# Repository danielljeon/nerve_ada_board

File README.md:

# nerve_ada_board

Nerve dev board using off-the-shelf modules.

> **Note: This design is now no longer under active development.** The final
> changes to the main branch are published as release tagged `v0.1.0-beta`, see
> the release notes: [1.1 v0.1.0-beta](#11-v010-beta).
>
> Successor: [`nerve_pcb`](https://github.com/danielljeon/nerve_pcb).

> 💡**Hint:** To clone this repository use:
> ```shell
> git clone --recursive
> ```

---

|                   KiCad Render                   |                   `v0.1.0-alpha-7b18788`                   |
|:------------------------------------------------:|:----------------------------------------------------------:|
|  |  |

---

<details markdown="1">
  <summary>Table of Contents</summary>

<!-- TOC -->
* [nerve_ada_board](#nerve_ada_board)
  * [1 Release Notes](#1-release-notes)
    * [1.1 v0.1.0-beta](#11-v010-beta)
      * [1.1.1 LSE Crystal](#111-lse-crystal)
      * [1.1.2 External Clock Crystal Tuning](#112-external-clock-crystal-tuning)
      * [1.1.3 GPS](#113-gps)
  * [2 Overview](#2-overview)
    * [2.1 Function Connectors](#21-function-connectors)
    * [2.2 Switches & Jumpers](#22-switches--jumpers)
    * [2.3 Plug-in Modules](#23-plug-in-modules)
    * [2.4 Breakout Connectors](#24-breakout-connectors)
  * [3 Development](#3-development)
    * [3.1 Worflow](#31-worflow)
    * [3.2 Submodules](#32-submodules)
  * [4 Production History](#4-production-history)
    * [4.1 v0.1.0-alpha-7b18788](#41-v010-alpha-7b18788)
<!-- TOC -->

</details>

---

## 1 Release Notes

### 1.1 v0.1.0-beta

Following the initial validation of components and software on this PCB design,
development has shifted to a more production-oriented
board: [nerve_pcb](https://github.com/danielljeon/nerve_pcb). While the base
components remain similar, many have been modified, with further
changes expected.

During the development of the new design, several hardware and PCB issues were
identified. Although this `README.md` will no longer be updated, the following
sections document the known issues as of the final release.

`v0.1.0-beta` is a slightly improved and updated version of an earlier
production run using `v0.1.0-alpha-7b18788`,
see [4.1 v0.1.0-alpha-7b18788](#41-v010-alpha-7b18788).

#### 1.1.1 LSE Crystal

The current LSE crystal on the STM32F446RE is the ABS25-32.768KHZ-6-T.

This is not the intended component; the correct crystal should have been the
`ABS25-32.768KHZ-T`, which has a more appropriate load capacitance specification
of 12.5 pF. The `ABS25-32.768KHZ-6-T` variant, with a 6 pF load capacitance, was
used inadvertently.

#### 1.1.2 External Clock Crystal Tuning

The crystal circuits use calculated capacitors that have not yet been fully
verified or fine-tuned. Specifically, the 32.768 kHz LSE crystal is likely using
incorrect capacitors with a value of 1.5 pF.

#### 1.1.3 GPS

The GPS module (`SAM-M10Q`) had not been verified to be functional as of the
release. However, this is likely due to software limitations rather than issues
with the hardware or PCB design.

---

## 2 Overview

Development board for the STM32
based [nerve](https://github.com/danielljeon/nerve) controller firmware.

### 2.1 Function Connectors

These connectors are fixed by hardware (PCB traces or the connector itself).

| Connector             | Ref | Description                                                                    |
|-----------------------|:---:|--------------------------------------------------------------------------------|
| Tag-Connect TC2050    | J1  | Programming/debug connector                                                    |
| Hinge microSD Card    | J2  | Portable storage, see [Molex product video](https://youtu.be/YY2V8z6UK7M?t=95) |
| USB-C 5 V Power       | J3  | Power only USB-C, primary 5 V source                                           |
| CR1220 Battery        | BT1 | MCU and GPS battery source 3.3 V supply                                        |
| CAN1 (Transceiver U7) | J7  | Pin 1: CAN1 High, Pin 2: CAN1 Low                                              |
| CAN2 (Transceiver U8) | J8  | Pin 1: CAN2 High, Pin 2: CAN2 Low                                              |

### 2.2 Switches & Jumpers

User controllable hardware and/or firmware driven inputs.

| Switch/Jumper           | Ref | Description                                    |
|-------------------------|:---:|------------------------------------------------|
| MCU NRESET Switch       | SW1 | Generic 6 mm TH button, push to reset          |
| MCU PA0 Switch          | SW2 | Generic 6 mm TH button, designed for SYS_WKUP0 |
| MCU PC13 Switch         | SW3 | Generic 6 mm TH button, designed for SYS_WKUP1 |
| SDIO Card Detect Jumper | J4  | Close for card inserted (pull-down on close)   |
| BOOT0 Jumper            | J5  | Open for run flash memory (pull-down on open)  |

### 2.3 Plug-in Modules

Off-the-shelf plug-in boards, primarily from Adafruit.

| Manufacturer Part Number |  Ref   | Manufacturer            | Hardware Interface | Quantity | Description                      |
|--------------------------|:------:|-------------------------|--------------------|---------:|----------------------------------|
| 4816                     |   U3   | Adafruit Industries LLC | 2.54 mm pitch TH   |        1 | BMP390 Module                    |
| Digi XBee-PRO 900HP      |   U5   | Digi                    | 2 mm pitch TH      |        1 | Long Range 900 MHz OEM RF Module |
| 4754                     |   U6   | Adafruit Industries LLC | 2.54 mm pitch TH   |        1 | BNO085 Module                    |
| 5708                     | U7, U8 | Adafruit Industries LLC | 2.54 mm pitch TH   |        2 | TJA1051T/3 Module                |

### 2.4 Breakout Connectors

Simple breakout connectors, driven fully or partially by firmware. See schematic
and firmware docs for details.

| Connector        | Ref | Logic | Description                                                                                     |
|------------------|:---:|:-----:|-------------------------------------------------------------------------------------------------|
| WS2812B Extender | J6  |  5 V  | Pin 1: PWM, Pin 2: Ground, use separate supply (preventing over current draw) and common ground |
| SPI Breakout     | J9  | 3.3 V | Pin 1: CS, Pin 2: SCK, Pin 3: MISO, Pin 4: MOSI                                                 |
| GPIO Breakout    | J10 |  5 V  | Pin 1, 2, 3: GPIO 1, 2, 3                                                                       |
| PWM Breakout     | J11 |  5 V  | Pin 1, 2: PWM 1, 2                                                                              |
| UART Camera      | J12 |  5 V  | Pin 1: 5 V, Pin 2: UART RX, Pin 3: UART TX, Pin 4: Ground, design for low current camera        |

---

## 3 Development

### 3.1 Worflow

Developed using KiCad with KiBot GitHub Actions
workflow, [kibot.yaml](.github/workflows/kibot.yaml).

- KiBot configurations found in [config.kibot.yaml](config.kibot.yaml).

CI/CD objectives:

1. ERC (Electrical Rule Check).
2. DRC (Design Rule Check).
3. PCB docs.
    - PCB layer docs (`.pdf` and `.svg`).
4. PCB manufacturing.
    - Gerber files (`.grb`).
    - Drill file (`.drl` and `.pdf` reference docs).
5. Assembly (fabrication service & hand assembly).
    - Pick-and-place assembly position file (`.pos`).
    - Component distributor ordering BoM (`.csv`).
    - General BoMs (`.xlsx` and `.html`).
    - Component placement guide (`.html`).
6. CAD.
    - (`.step`).

### 3.2 Submodules

This repository includes the submodule `component_library`, located
at: [component_library](https://github.com/danielljeon/component_library).

When cloning the repository, make sure to use the recursive option:

```shell
git clone --recursive
```

To update the submodule to its latest version in a cloned repository, use the
following command:

> Note: This is not recommended for this deprecated repository, as pulling
> updates from the submodule's latest commit may result in incompatibilities.

```shell
git submodule update --remote --merge
```

---

## 4 Production History

### 4.1 v0.1.0-alpha-7b18788

> Note: This production run was not marked as a (pre)release due to very high
> probability of bring-up issues as it was one of my first PCB designs.

Commit: [7b18788](https://github.com/danielljeon/nerve_ada_board/commit/7b187884c03f280627d8443d2d9cc163f4b6956e).

<details markdown="1">
  <summary>Manufacturing & Assembly Details</summary>

**Manufacturing Information:**

Production date: 2024-10-22.

- Manufacturer: JLCPCB.
- Order: PCB, stencil.
- PCB specs (non-default):
    - PCB quantity: 5.
    - Surface Finish: LeadFree HASL.
    - Impedance control stackup: `JLC041611-7628`.
        - Outer Copper Weight: 1 oz.
        - Inner Copper Weight: 1 oz.
- Stencil specs (non-default):
    - Stencil quantity: 1.
    - Custom size: 100 mm x 100 mm (matching PCB dimensions).

**Assembly Information:**

Assembly date: 2024-11-09 to 2024-11-13.

- Assembled PCB quantity: 2.
- Process:
    - Stencil solder paste print by hand & soldering iron.
        - Solder paste: Chip Quik TS391LT `Bi57.6Sn42Ag0.4`.
    - SMD pick-and-place by hand.
    - Reflow with oven.
        - Roughly correct temperatures to solder paste docs.
        - Approximately doubled soak time due to oven limitations.

1. PCB 1 Notes:
    - Components: All placed except for GPS.
    - Damage to though holes for connector J4 mostly on bottom side.
        - First assembly was unsatisfactory.
        - Attempt to remove solder to reassemble header pins resulted in damage
          from aggressive force with the soldering iron.
        - Final result was functional, but the board damage remains on bottom
          side.
            - Suggested correction: heat soak the board, note also left in board
              evaluation section of this writeup.
        - Continuity tests showed no issues after completion.
    - Bridged pins on the U2 (STM32F446RE).
        - Likely too much solder paste and less than ideal definition of the
          printed solder paste.
        - Resolved with flux and reheat with soldering iron as well as use of
          solder wick.
            - Suggested correction: Cleaner swipe of the stencil with less
              solder paste.
2. PCB 2 Notes:
    - Components: All placed.
    - Misplacement of U2 (STM32F446RE).
        - Component shifted seemingly during reflow, some sides of the MCU had
          short or unconnected pins.
        - There was likely too much solder as well as potential misalignment
          during the pick-and-place by hand.
        - Attempts were made to reposition the component.
        - Some solder mask was removed near the pads, however no significant
          functional concerns were visible.
        - In order to limit potential damage to the board or components (
          particularly the expensive GPS module), the component was removed.
        - No pad damage was visible.
        - A replacement component was hand soldered with a soldering iron.
            - Suggested correction: Improve solder paste printing (again) and
              better hand placement. If too much paste was visible retry before
              any reflow. Perhaps, even holding the component in position with
              thin strips of kapton tape.
    - Bridged pins on the U9, U10 (TXB0104QPWRQ1).
        - Same details as U2 on PCB 1 (see above).
    - U4 GPS module solder joints are not visible (pads under component), but a
      continuity test of nets in every combination pair showed no shorts.

</details>

**Board Evaluation:**

- Large planes, especially ground. It is difficult to adjust through hole
  components that have ground pin(s).
    - Requires heat soaked board or potentially risky soldering iron
      temperatures.
- Some components such as resistors or capacitors are very close to through hole
  header pin connectors/jumpers.
    - Not super difficult to deal with, but something to keep in mind.
- The XBee Pro 900HP can cause clearance issues when trying to press-release the
  nearby TC2050-IDC's plastic clips.
- The Molex 472192001 hinge microSD card slot is functional, but slightly
  blocked by the Adafruit TJA1051T/3 breakout board.
    - This Would be easily resolved by implementing CAN circuit/components
      directly onto the PCB.

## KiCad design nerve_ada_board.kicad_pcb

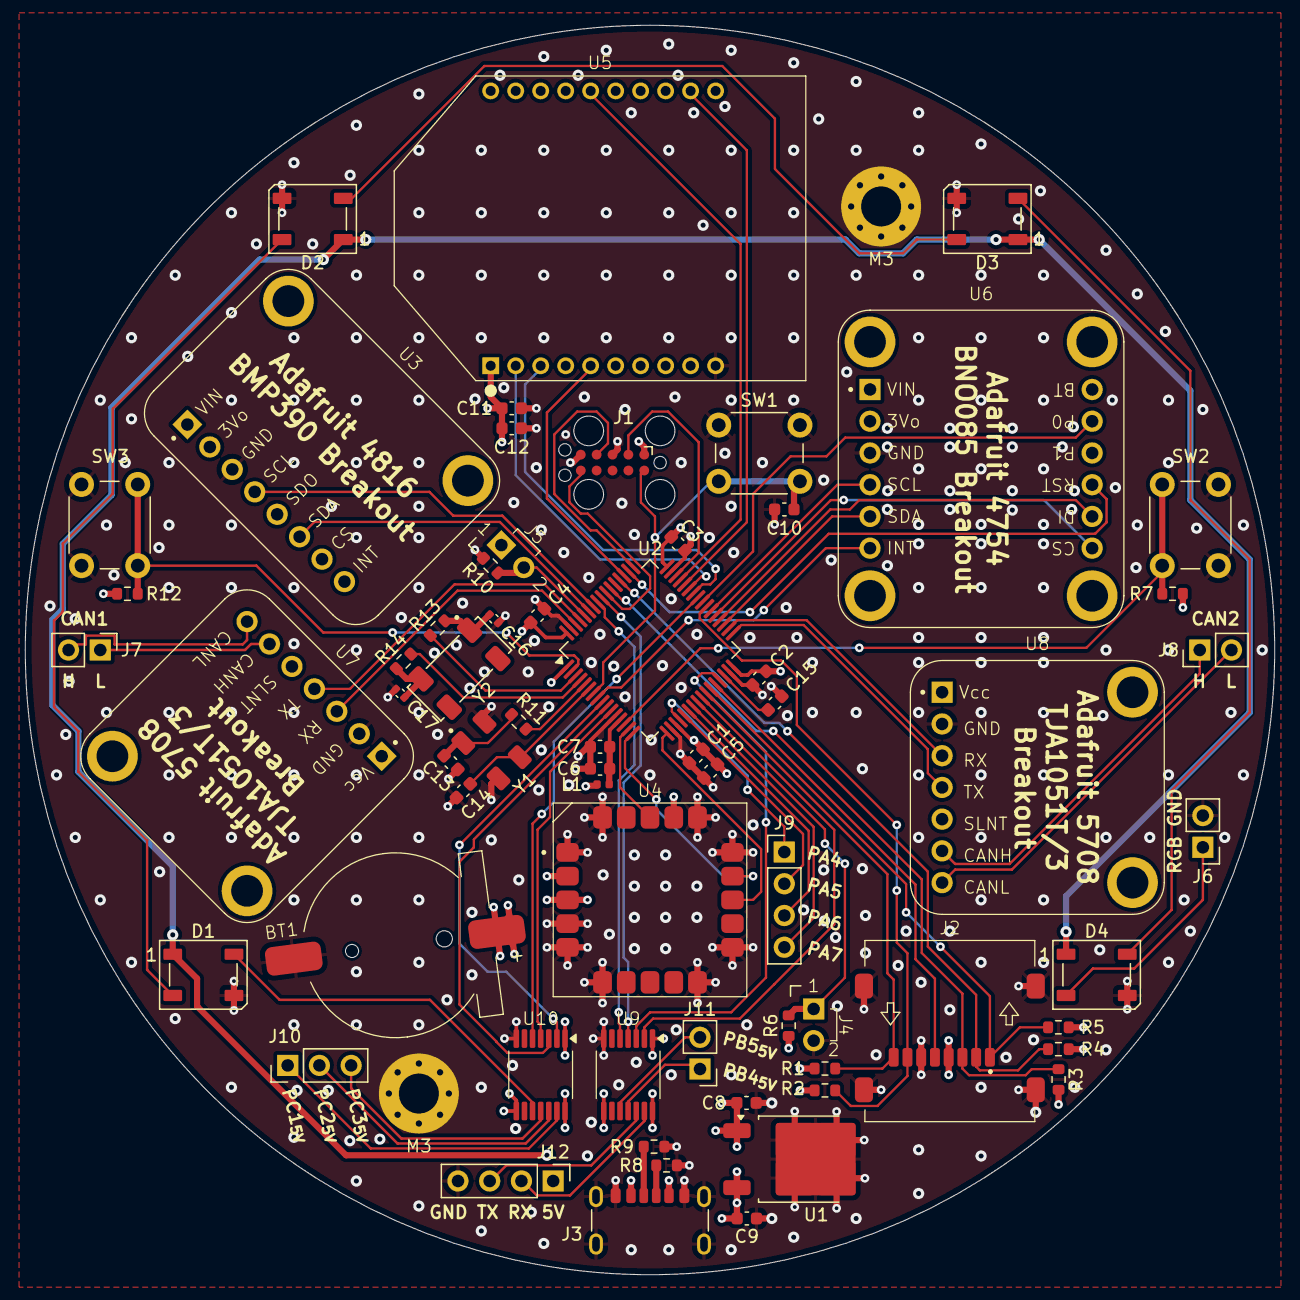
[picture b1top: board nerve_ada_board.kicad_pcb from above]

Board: 4 copper layers, 100.0 x 100.0 mm, 66 parts (0 on the bottom side), 78 nets.

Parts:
BT1: CR1220; harwin_s8411-45r_cr1220_battery
C1, C2, C3, C4, C10: 100n; C_0603_1608Metric
C5: 4u7; C_0603_1608Metric
C6, C8, C12: 1u; C_0603_1608Metric
C7: 10n; C_0603_1608Metric
C9, C15: 2u2; C_0603_1608Metric
C11: 47p; C_0603_1608Metric
C13, C14: 20p; C_0603_1608Metric
C16, C17: 1p5; C_0402_1005Metric
D1, D2, D3, D4: WS2812B; LED_WS2812B_PLCC4_5.0x5.0mm_P3.2mm
H1, H2: M3; MountingHole_3.2mm_M3_Pad_Via
J1: TC2050-IDC; tag_connect_tc2050-idc
J2: 472192001; molex_472192001_microsd_hinge
J3: 2171750001; molex_2171750001_usb_c_6p
J4, J5: harwin_2p_2-54_jumper_open
J6: WS2812B; PinHeader_1x02_P2.54mm_Vertical
J7: CAN1; PinHeader_1x02_P2.54mm_Vertical
J8: CAN2; PinHeader_1x02_P2.54mm_Vertical
J9: PA4-7; PinHeader_1x04_P2.54mm_Vertical
J10: PC1-3; PinHeader_1x03_P2.54mm_Vertical
J11: PB4-5; PinHeader_1x02_P2.54mm_Vertical
J12: Camera; PinHeader_1x04_P2.54mm_Vertical
L1: 39n; L_0402_1005Metric
R1, R2, R3, R4, R5: 47k; R_0603_1608Metric
R6, R7, R10, R12: 10k; R_0603_1608Metric
R8, R9: 5k1; R_0603_1608Metric
R11, R13, R14: 0R; R_0603_1608Metric
SW1, SW2, SW3: SPST; SW_PUSH_6mm
U1: ld39150dt33-r; to-252-2_dpak-2-leg
U2: STM32F446RET; LQFP-64_10x10mm_P0.5mm
U3: adafruit_4816_bmp390
U4: SAM-M10Q; ublox_sam
U5: XBP9B-DMWT-002; xbee_pro_900hp
U6: adafruit_4754_bno085
U7, U8: adafruit_5708_tja1051t-3
U9, U10: TXB0104QPWRQ1; txb0104qpwrq1
Y1: 8M; xtal_abm3b-8.000mhz-10-1-u-t
Y2: 32k768; xtal_abs25-32.768khz-6-t

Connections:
+3.3VA: C6.1, C7.1, L1.2, U2.13 (VDDA)
+3.3VBATT: BT1.2, U2.1 (VBAT), U4.3 (V_BCKP)
+3V3: C1.1, C2.1, C3.1, C4.1, C5.1, C9.1, C11.1, C12.1, J1.1 (VCC), J2.4 (VDD), J5.1, L1.1, R1.1, R2.1, R3.1, R4.1, R5.1, R6.1, R7.1, R12.1, U1.3 (VO), U2.19 (VDD), U2.32 (VDD), U2.48 (VDD), U2.64 (VDD), U3.1 (VIN), U4.2 (V_IO), U4.17 (VCC), U5.1 (VCC), U5.14 (VREF), U6.1 (VIN), U6.10 (P1), U7.1 (Vcc), U8.1 (Vcc), U9.1 (V_{CCA}), U9.8 (OE), U10.1 (V_{CCA}), U10.8 (OE)
+5V: C8.1, D1.1 (VDD), D2.1 (VDD), D3.1 (VDD), D4.1 (VDD), J3.A9 (VBUS), J3.B9 (VBUS), J12.1, U1.1 (VI), U9.14 (V_{CCB}), U10.14 (V_{CCB})
/BOOT0: J5.2, R10.2, U2.60 (BOOT0)
/CAMERA_RX: J12.2, U9.13 (B1)
/CAMERA_TX: J12.3, U9.12 (B2)
/CAN1+: J7.1, U7.6 (CANH)
/CAN1-: J7.2, U7.7 (CANL)
/CAN1_RX: U2.61 (PB8), U7.4 (TX)
/CAN1_TX: U2.62 (PB9), U7.3 (RX)
/CAN2+: J8.1, U8.6 (CANH)
/CAN2-: J8.2, U8.7 (CANL)
/CAN2_RX: U2.33 (PB12), U8.4 (TX)
/CAN2_TX: U2.34 (PB13), U8.3 (RX)
/EXTI0_IMU_INT: U2.8 (PC0), U6.6 (INT)
/GPIO_GPS_RST: U2.15 (PA1), U4.18 (RESET_N)
/GPIO_IMU_P0: U2.40 (PC9), U6.11 (P0)
/GPIO_IMU_RST: U2.50 (PA15), U6.9 (RST)
/GPIO_RADIO_RST: U2.51 (PC10), U5.5 (~RESET)
/GPIO_SPI2_CS: U2.37 (PC6), U6.7 (CS)
/HSE_IN: R11.1, U2.5 (PH0_OSC_HSE_IN)
/HSE_OUT: C14.1, U2.6 (PH1_OSC_HSE_OUT), Y1.3
/I2C1_SCL: U2.58 (PB6), U3.4 (SCL)
/I2C1_SDA: U2.59 (PB7), U3.6 (SDA)
/LSE_IN: R13.1, U2.3 (PC14_OSC32_LSE_IN)
/LSE_OUT: R14.1, U2.4 (PC15_OSC32_LSE_OUT)
/NRST: C10.2, J1.10 (~RESET), SW1.2, U2.7 (NRST)
/PA4: J9.1, U2.20 (PA4)
/PA5: J9.2, U2.21 (PA5)
/PA6: J9.3, U2.22 (PA6)
/PA7: J9.4, U2.23 (PA7)
/PB4: U2.56 (PB4), U9.4 (A3)
/PB4_EXP: J11.1, U9.11 (B3)
/PB5: U2.57 (PB5), U9.5 (A4)
/PB5_EXP: J11.2, U9.10 (B4)
/PC1: U2.9 (PC1), U10.2 (A1)
/PC1_EXP: J10.1, U10.13 (B1)
/PC2: U2.10 (PC2), U10.3 (A2)
/PC2_EXP: J10.2, U10.12 (B2)
/PC3: U2.11 (PC3), U10.4 (A3)
/PC3_EXP: J10.3, U10.11 (B3)
/RGB_LED: D1.4 (DIN), U10.10 (B4)
/SDIO_CLK: J2.5 (CLK), U2.28 (PB2)
/SDIO_CMD: J2.3 (CMD), R3.2, U2.54 (PD2)
/SDIO_D0: J2.7 (DAT0), R2.2, U2.39 (PC8)
/SDIO_D1: J2.8 (DAT1), R1.2, U2.26 (PB0)
/SDIO_D2: J2.1 (DAT2), R5.2, U2.27 (PB1)
/SDIO_D3: J2.2 (DAT3/CD), R4.2, U2.52 (PC11)
/SDIO_DET: J4.1, R6.2, U2.24 (PC4)
/SPI2_MISO: U2.35 (PB14), U6.5 (SDA)
/SPI2_MOSI: U2.36 (PB15), U6.8 (DI)
/SPI2_SCK: U2.38 (PC7), U6.4 (SCL)
/SWCLK: J1.4 (SWCLK/TCK), U2.49 (PA14)
/SWDIO: J1.2 (SWDIO/TMS), U2.46 (PA13)
/SWO: J1.6 (SWO/TDO), U2.55 (PB3)
/TIM1_CH1_PWM: U2.41 (PA8), U10.5 (A4)
/USART1_CTS: U2.44 (PA11), U5.12 (~CTS/DIO7)
/USART1_RTS: U2.45 (PA12), U5.16 (~RTS/DIO6)
/USART1_RX: U2.43 (PA10), U5.2 (DOUT/DIO13)
/USART1_TX: U2.42 (PA9), U5.3 (DIN/~CONFIG/DIO14)
/USART2_RX: U2.17 (PA3), U4.13 (TXD)
/USART2_TX: U2.16 (PA2), U4.14 (RXD)
/USART3_RX: U2.25 (PC5), U9.2 (A1)
/USART3_TX: U2.29 (PB10), U9.3 (A2)
GND: BT1.1, C1.2, C2.2, C3.2, C4.2, C5.2, C6.2, C7.2, C8.2, C9.2, C10.1, C11.2, C12.2, C13.2, C14.2, C15.2, C16.2, C17.2, D1.3 (VSS), D2.3 (VSS), D3.3 (VSS), D4.3 (VSS), H1.1, H2.1, J1.3 (GND), J1.5 (GND/VPROG), J2.6 (VSS), J2.G1 (GND), J2.G2 (GND), J2.G3 (GND), J2.G4 (GND), J3.A12 (GND), J3.B12 (GND), J3.S1 (SHIELD), J4.2, J6.2, J12.4, R8.2, R9.2, R10.1, SW1.1, SW2.2, SW3.1, U1.2 (GND), U2.12 (VSSA), U2.18 (VSS), U2.31 (VSS), U2.47 (VSS), U2.63 (VSS), U3.3 (GND), U4.1 (GND), U4.4 (GND), U4.5 (GND), U4.6 (GND), U4.10 (GND), U4.11 (GND), U4.15 (GND), U4.16 (GND), U4.20 (GND), U5.10 (GND), U6.3 (GND), U7.2 (GND), U8.2 (GND), U9.7 (GND), U10.7 (GND), Y1.2, Y1.4
unnamed: C13.1, R11.2, Y1.1
unnamed: C16.1, R13.2, Y2.1
unnamed: C17.1, R14.2, Y2.2
unnamed: D1.2 (DOUT), D2.4 (DIN)
unnamed: D2.2 (DOUT), D3.4 (DIN)
unnamed: D3.2 (DOUT), D4.4 (DIN)
unnamed: D4.2 (DOUT), J6.1
unnamed: J3.A5 (CC1), R9.1
unnamed: J3.B5 (CC2), R8.1
unnamed: R7.2, SW2.1, U2.14 (PA0)
unnamed: R12.2, SW3.2, U2.2 (PC13)
unnamed: C15.1, U2.30 (VCAP_1)

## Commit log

2024-09-05 Add license file
2024-09-05 Add gitignore for KiCad
2024-09-05 Add KiBot workflow
2024-09-29 Add component_library submodule
2024-09-29 Update components submodule
2024-09-30 Add initial WIP design
2024-10-01 Update component_library
2024-10-01 Add WIP basics, power and sensors
2024-10-03 Add XBee radio and u-blox GPS
2024-10-04 Add very early full schematic
2024-10-05 Clean up schematic
2024-10-05 Add WS2812B RGB LEDs
2024-10-05 Remove battery jumpers and fix WS2812B power
2024-10-06 Update and organize symbols on schematic
2024-10-06 Add level shifter and buzzer, organize schematic
2024-10-06 Update library, fix power circuits, clean up
2024-10-06 Update symbols from library
2024-10-06 Update jumper with library, clean up
2024-10-06 Pass ERC, add final MCU breakouts, clean up
2024-10-06 Clean up REF annotation sequence
2024-10-06 Update library and LSE crystal on schematic
2024-10-06 Switch to hierarchical labels and major clean up
2024-10-06 Update library and fix annotations
2024-10-07 Update power circuits and minor clean up
2024-10-08 Update component library and schematic
2024-10-08 Update component library and schematic HSE
2024-10-08 Clean up annotations and remove bad net label
2024-10-09 Update component_library and schematic
2024-10-09 Add second level shifter and clean up
2024-10-10 Improve expansion peripherals and remove buzzer
2024-10-10 Add connector footprints
2024-10-10 Change to jumper based BOOT0
2024-10-10 Update annotations
2024-10-11 Assign capacitor, resistor, inductor footprints
2024-10-14 Fix bad net label
2024-10-14 Add WIP PCB layout
2024-10-14 Update stackup and board setup for fab
2024-10-14 Add SWD, PWR and GND netclasses
2024-10-14 Update board setup and organize basic netclasses
2024-10-14 Add ground planes
2024-10-14 Add CAN net labels for PCB diff pair
2024-10-15 Add WIP PCB, pass DRC
2024-10-16 Remove breakout GPIO PC12
2024-10-16 Clean up power plane, repass DRC, minor fixes
2024-10-16 Attempt workflow improvement
2024-10-16 Attempt fix workflow Kibot cache 3D files
2024-10-16 Add missing Kibot workflow cache step
2024-10-16 Add symbol and footprint library tables
2024-10-16 Attempt fix Kibot lib_footprint_mismatch
2024-10-16 Attempt 2, Kibot lib_footprint_mismatch
2024-10-16 Attempt 3, Kibot lib_footprint_mismatch
2024-10-16 Attempt 4, Kibot lib_footprint_mismatch
2024-10-16 Update config.kibot.yaml, finalize BoM fields
2024-10-16 Plane 1 ground pour and pass DRC
2024-10-16 Update component library and footprints on PCB
2024-10-16 Attempt 5, Kibot lib_footprint_mismatch
2024-10-16 Update CR1220 battery holder component
2024-10-17 Update CR1220 component, again
2024-10-17 Update CR1220 component, again 3
2024-10-17 Resolve ERC duplicate labelling warning
2024-10-17 Update config.kibot.yaml to lower PDF scaling
2024-10-17 Fix CODEOWNERS and update component_library
2024-10-19 Flight ready alpha and update components
2024-10-19 Fix SDIO card detect for active low
2024-10-19 Swap to LD39150DT33-R regulator
2024-10-20 Clean up layout around SDIO
2024-10-20 Move LEDs to 4 corners, cleanup layout
2024-10-20 Add mounting holes and cleanup layout
2024-10-21 Update component_library and PCB
2024-10-21 Add GND plane stitching and cleanup layout
2024-10-21 Final cleanup, fix stackup, adjust page docs
2024-10-23 Attempt fix KiBot CSV BOM
2024-10-23 Attempt fix KiBot CSV BOM 2
2024-10-23 Attempt fix KiBot CSV BOM 3
2024-10-23 Adjust KiBot CSV BOM for part quotes
2024-10-25 Cleanup KiBot config file
2024-10-25 Add README.md docs and add board picture
2024-10-30 Clean up silkscreen, fill mounting hole reliefs
2024-10-30 Update README.md generic docs
2024-10-30 Update J6 WS2812B connector pin order
2024-11-09 Add board assembly and evaluation docs
2024-11-09 Update TOC to JetBrains implementation
2024-11-09 Update component_library submodule
2024-11-10 Correct SDIO jumper docs
2024-11-11 Correct SDIO jumper docs (again)
2024-11-12 Update component library and docs picture
2024-11-12 Attempt fix WS2812B footprint mismatch warning
2024-11-12 Attempt fix WS2812B footprint mismatch warning 2
2024-11-12 Attempt fix WS2812B footprint mismatch warning 3
2024-11-14 Update production history
2024-11-21 Update component_library and propagate changes
2024-11-21 Update PCB docs picture
2024-11-22 Remove thermal reliefs on mounting holes
2024-11-22 Fix breakout header silkscreen labels
2024-11-22 Update docs picture
2024-12-03 Remove outdated README.md note
2024-12-03 Update KiBot workflow
2024-12-09 Update README.md for v0.1.0-beta
2025-05-14 Pre-archive edit to README.md and docs
